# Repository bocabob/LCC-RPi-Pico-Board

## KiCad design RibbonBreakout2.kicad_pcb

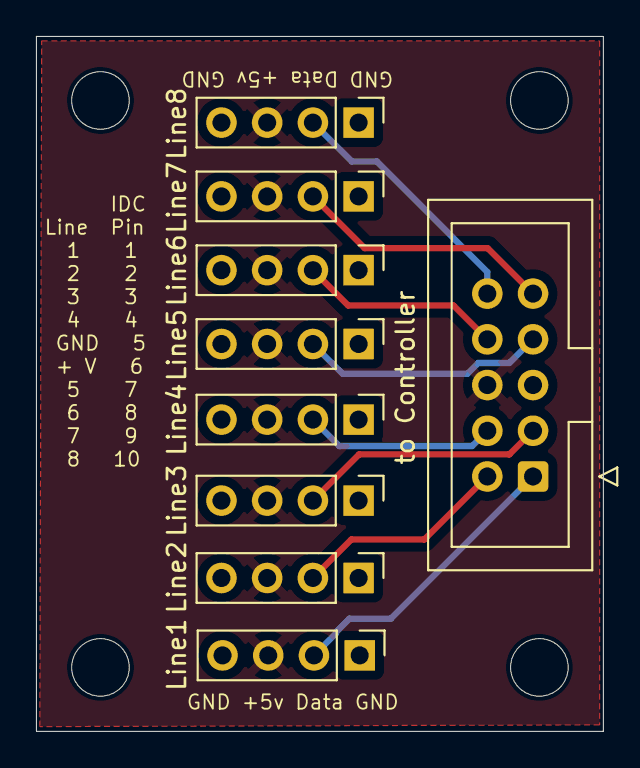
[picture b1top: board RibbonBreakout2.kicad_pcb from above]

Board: 2 copper layers, 31.5 x 38.6 mm, 9 parts (0 on the bottom side), 10 nets.

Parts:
Line1, Line2, Line3, Line4, Line5, Line6, Line7, Line8: Header; PinHeader_1x04_P2.54mm_Vertical
S1: Conn_02x05_Odd_Even; IDC-Header_2x05_P2.54mm_Vertical

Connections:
+5v: Line1.3, Line2.3, Line3.3, Line4.3, Line5.3, Line6.3, Line7.3, Line8.3, S1.6
GND: Line1.1, Line1.4, Line2.1, Line2.4, Line3.1, Line3.4, Line4.1, Line4.4, Line5.1, Line5.4, Line6.1, Line6.4, Line7.1, Line7.4, Line8.1, Line8.4, S1.5
Line1: Line1.2, S1.1
Line2: Line2.2, S1.2
Line3: Line3.2, S1.3
Line4: Line4.2, S1.4
Line5: Line5.2, S1.7
Line6: Line6.2, S1.8
Line7: Line7.2, S1.9
Line8: Line8.2, S1.10

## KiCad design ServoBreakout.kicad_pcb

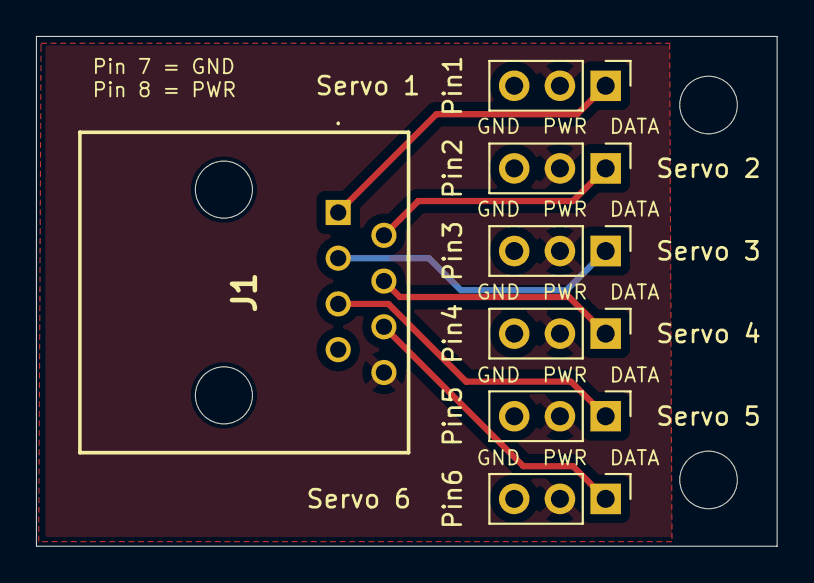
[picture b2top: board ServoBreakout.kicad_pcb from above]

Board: 2 copper layers, 41.1 x 28.3 mm, 7 parts (0 on the bottom side), 8 nets.

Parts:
J1: RJ45; MTJ880X1
Pin1: Servo 1; PinHeader_1x03_P2.54mm_Vertical
Pin2: Servo 2; PinHeader_1x03_P2.54mm_Vertical
Pin3: Servo 3; PinHeader_1x03_P2.54mm_Vertical
Pin4: Servo 4; PinHeader_1x03_P2.54mm_Vertical
Pin5: Servo 5; PinHeader_1x03_P2.54mm_Vertical
Pin6: Servo 6; PinHeader_1x03_P2.54mm_Vertical

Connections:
+5V: J1.8, Pin1.2, Pin2.2, Pin3.2, Pin4.2, Pin5.2, Pin6.2
Data 1: J1.1, Pin1.1
Data 2: J1.2, Pin2.1
Data 3: J1.3, Pin3.1
Data 4: J1.4, Pin4.1
Data 5: J1.5, Pin5.1
Data 6: J1.6, Pin6.1
GND: J1.7, Pin1.3, Pin2.3, Pin3.3, Pin4.3, Pin5.3, Pin6.3
